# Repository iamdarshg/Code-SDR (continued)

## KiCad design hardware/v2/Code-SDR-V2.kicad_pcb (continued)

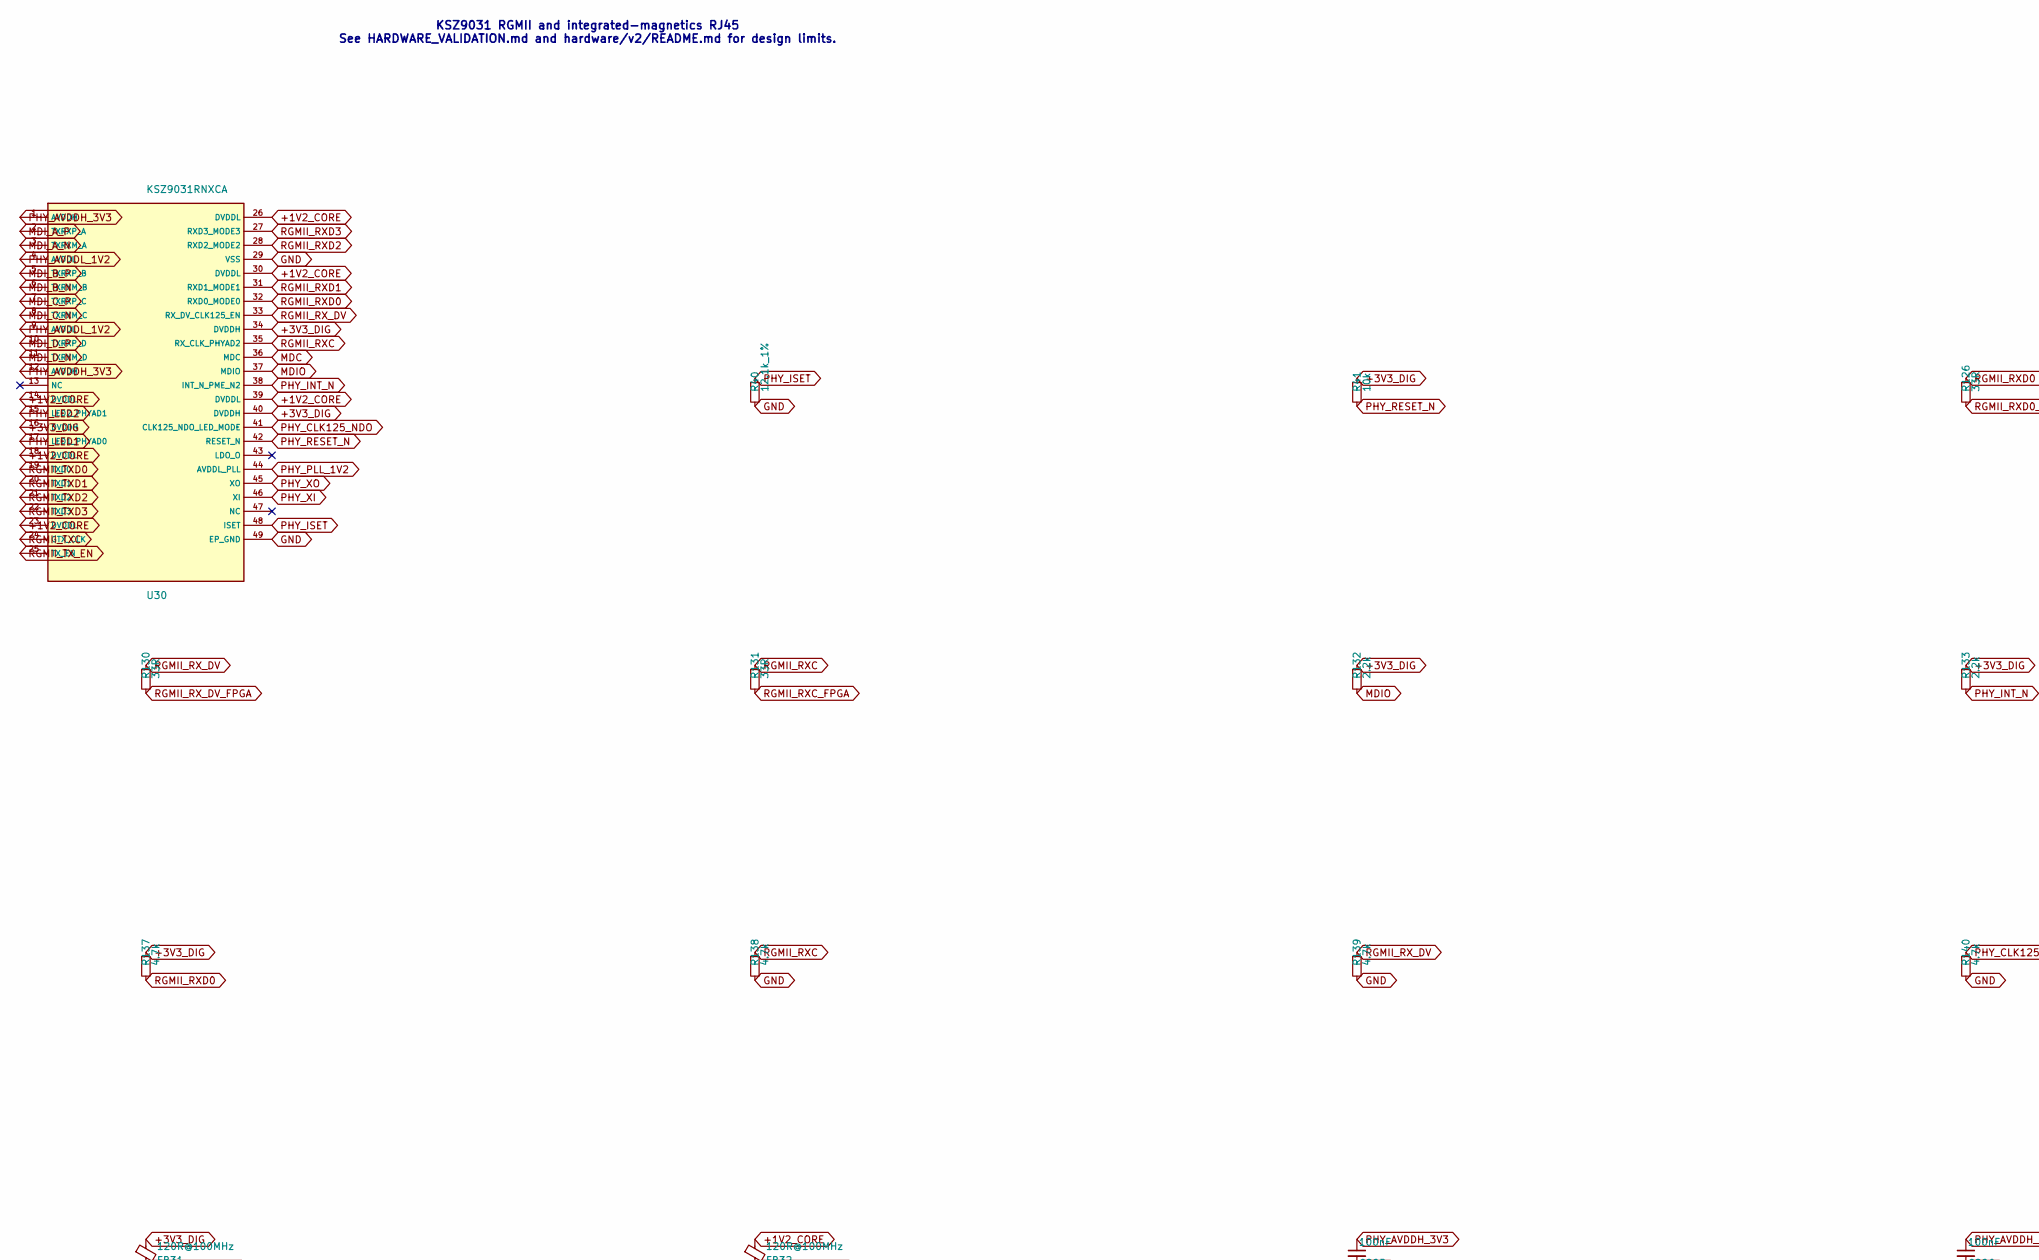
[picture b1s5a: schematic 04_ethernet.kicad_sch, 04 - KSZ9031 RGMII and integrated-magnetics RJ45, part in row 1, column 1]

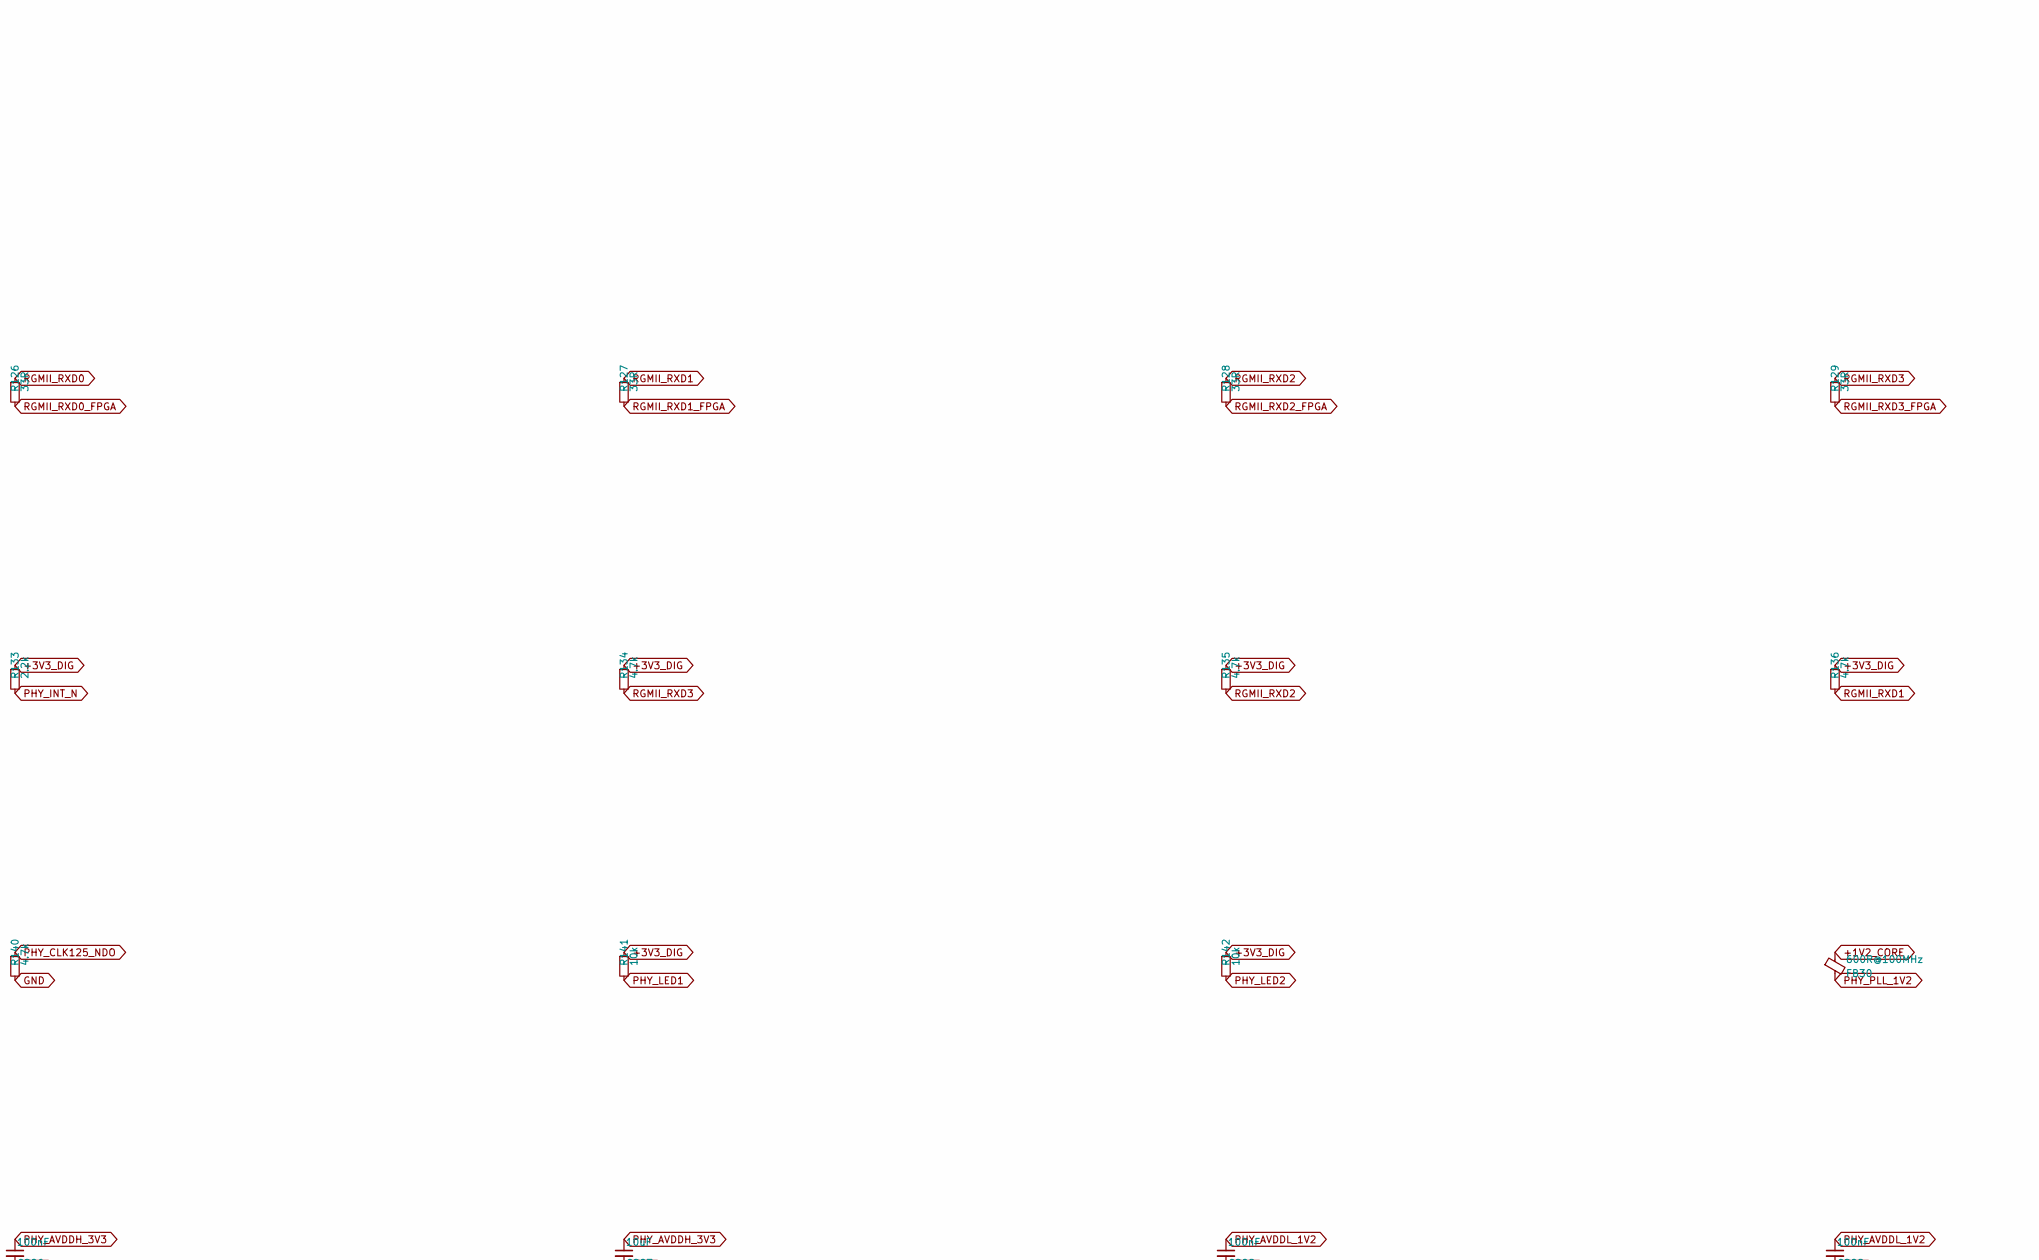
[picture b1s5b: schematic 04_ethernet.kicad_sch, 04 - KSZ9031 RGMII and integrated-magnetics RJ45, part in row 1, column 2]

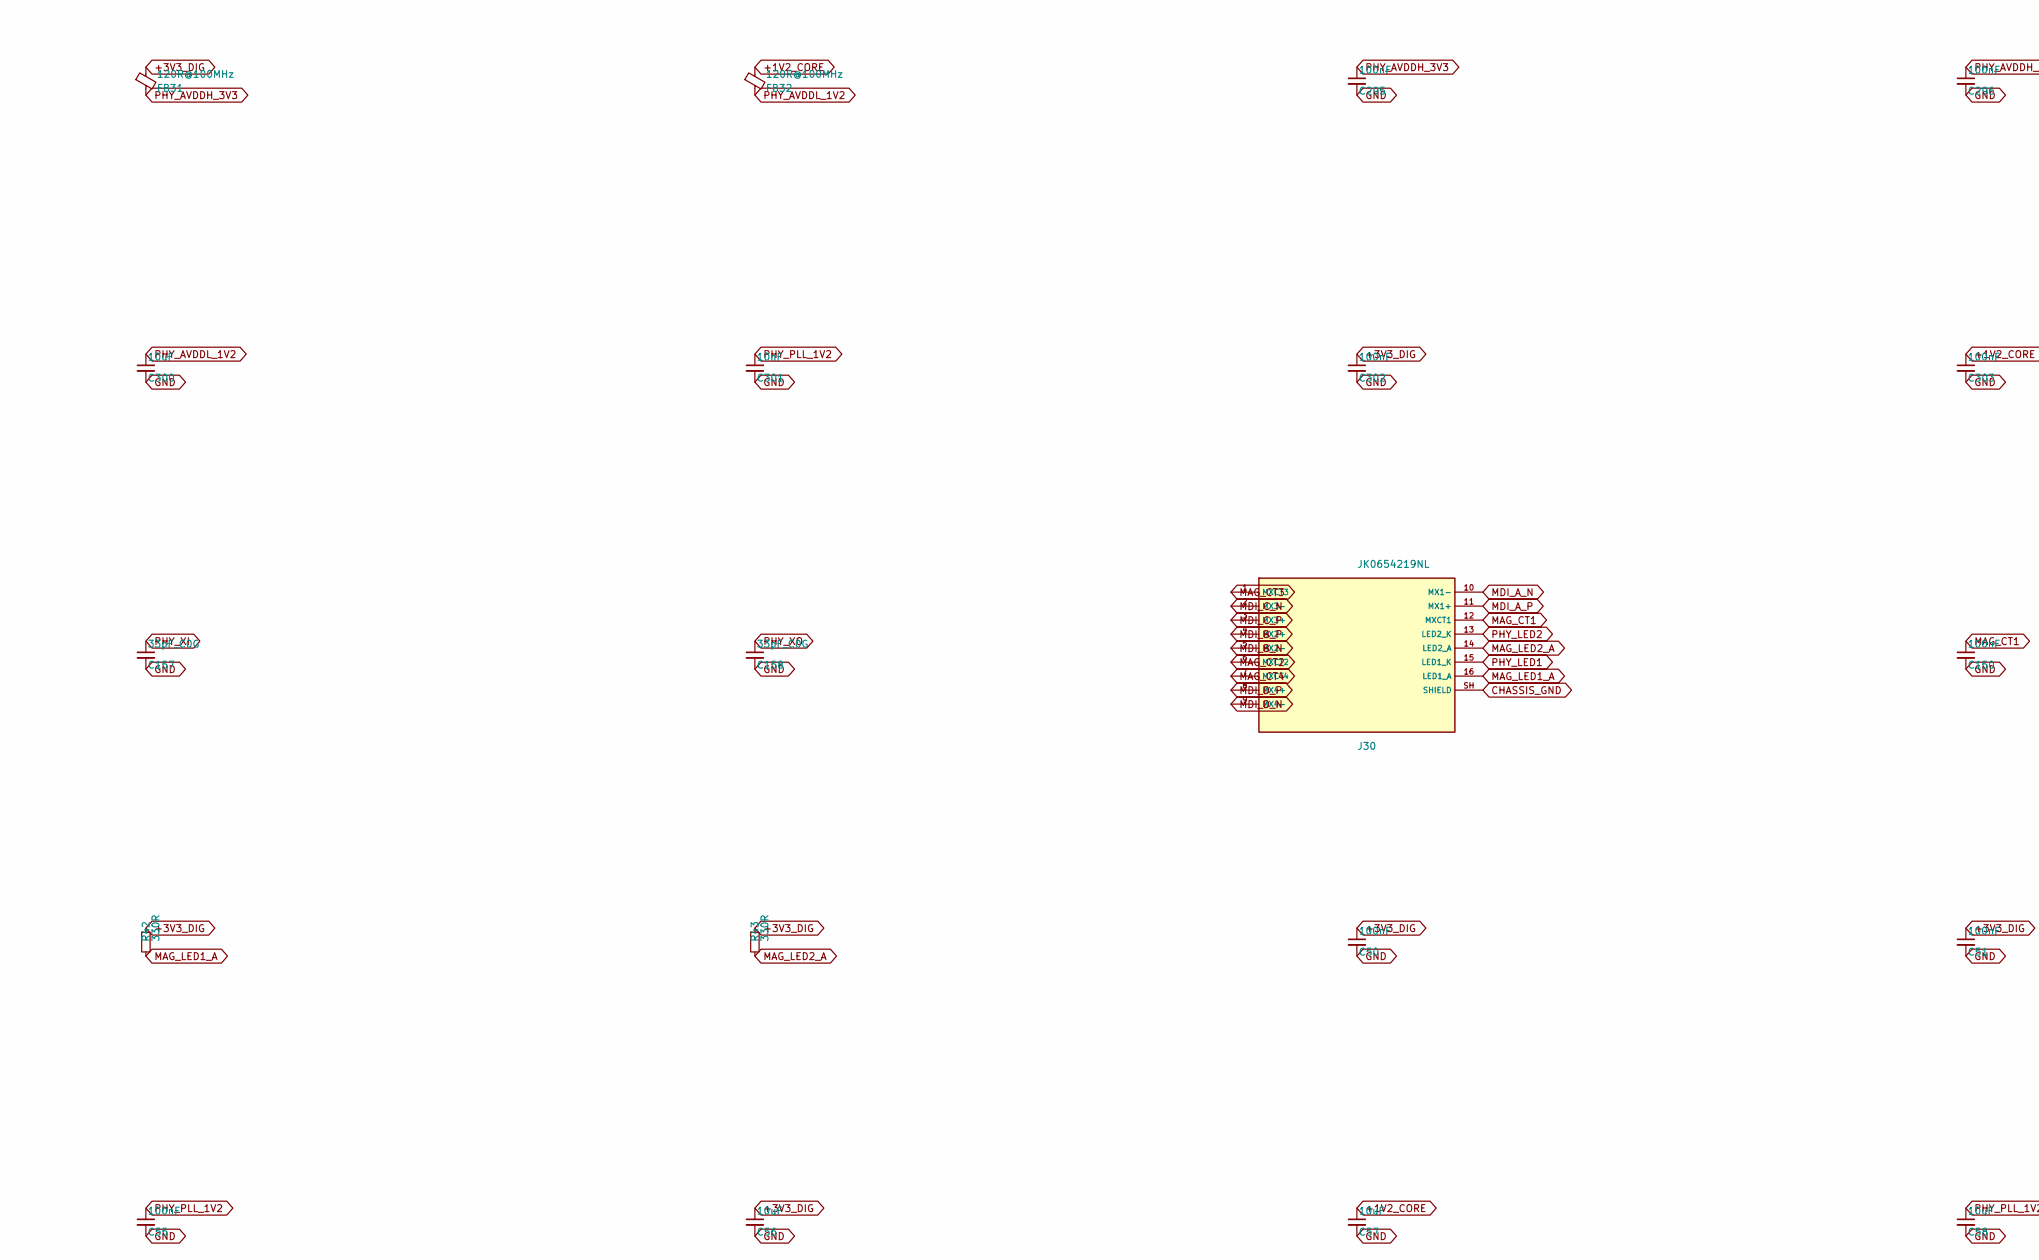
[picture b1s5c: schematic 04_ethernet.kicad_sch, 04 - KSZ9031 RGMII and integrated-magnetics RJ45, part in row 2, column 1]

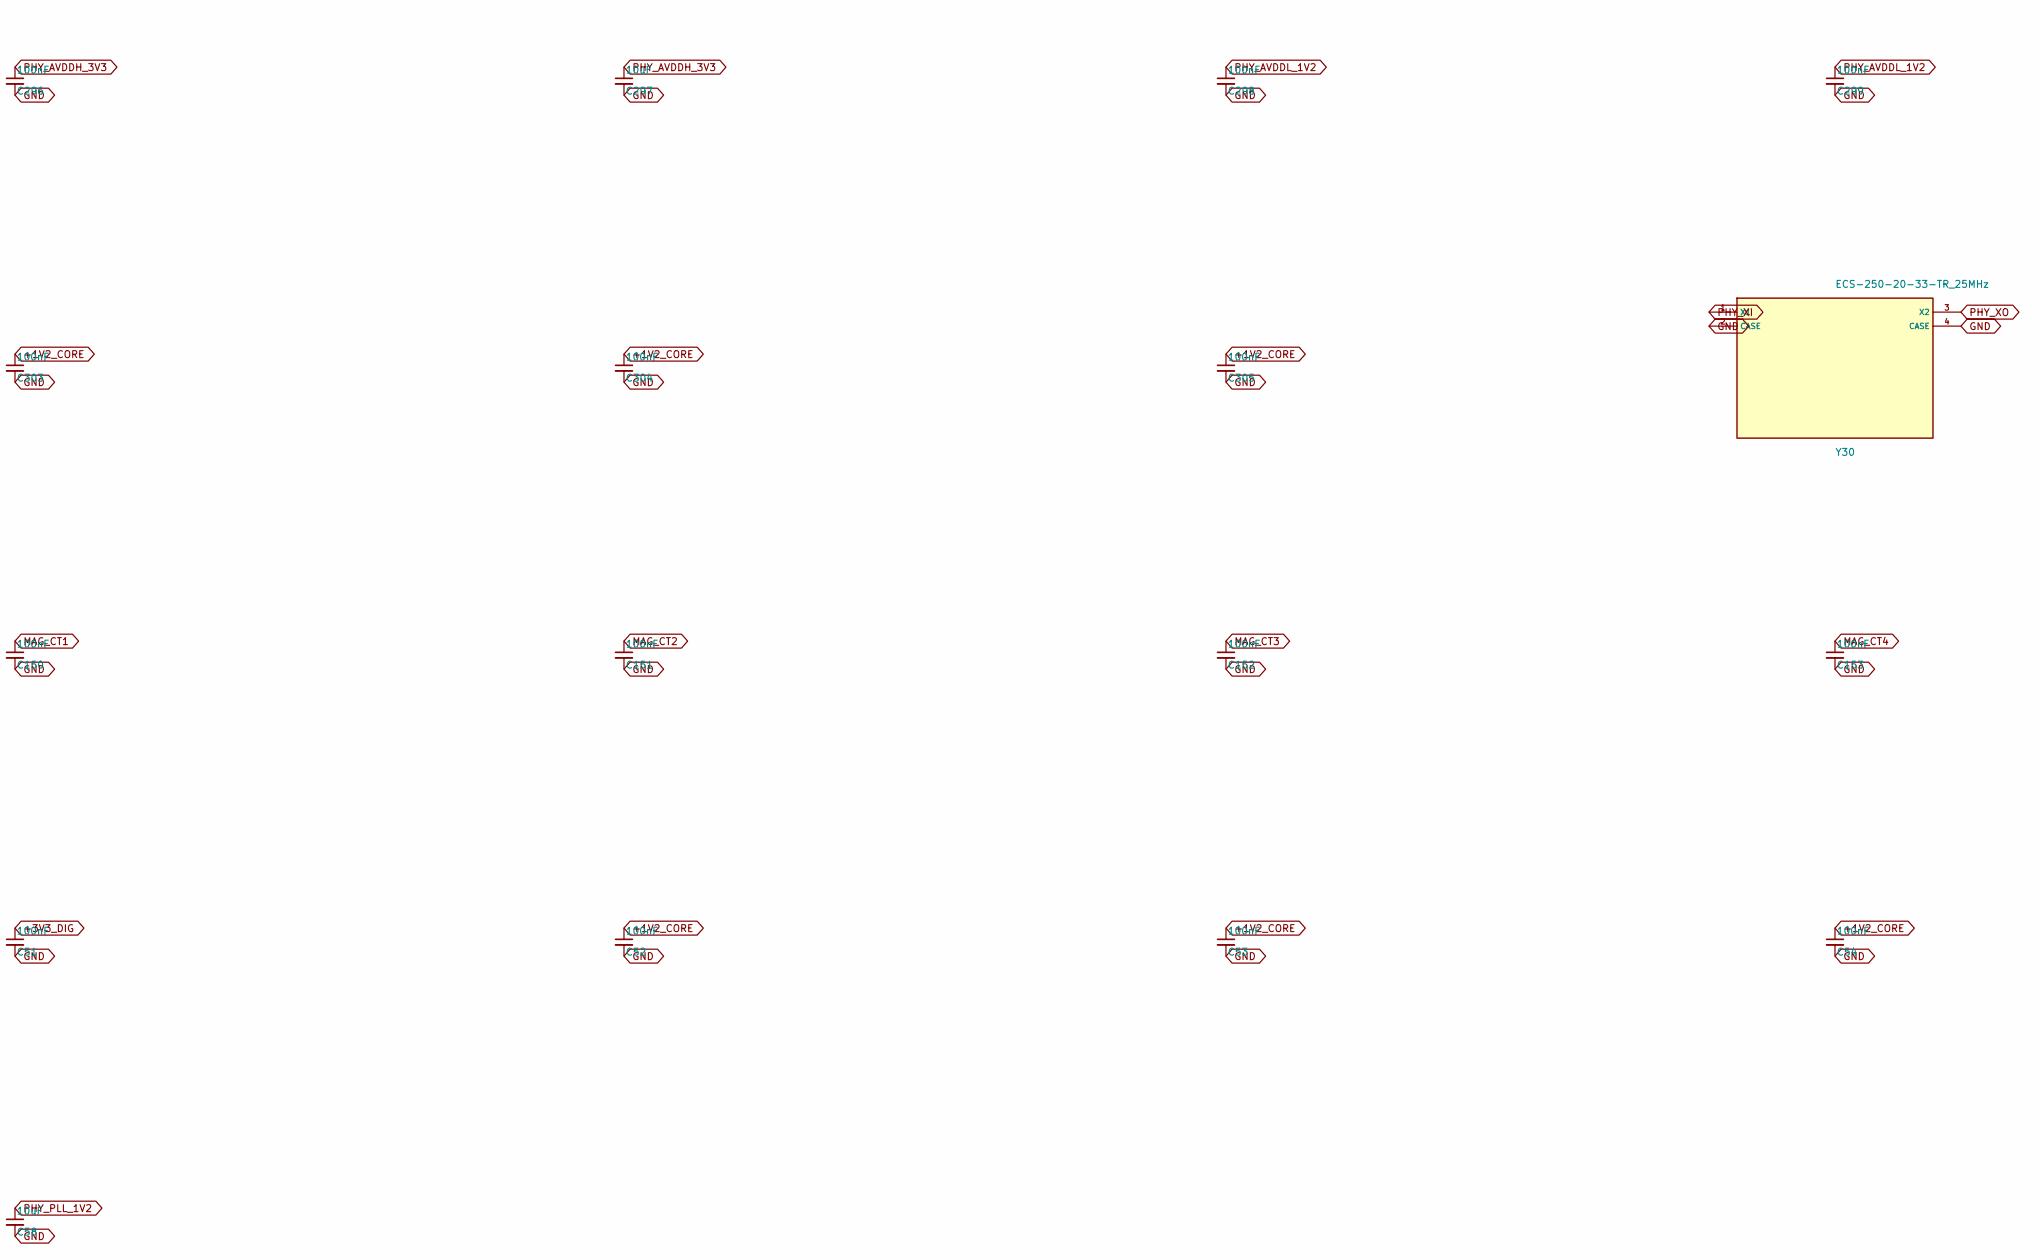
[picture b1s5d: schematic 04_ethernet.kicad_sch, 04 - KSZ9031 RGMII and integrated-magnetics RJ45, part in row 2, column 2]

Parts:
C50, C51, C52, C53, C54, C55, C150, C151, C152, C153, C295, C296, C298, C299, C302, C303, C304, C305: 100nF; C_0402_1005Metric
C56, C57, C58, C297, C300: 10uF; C_0805_2012Metric
C157, C158: 33pF_C0G; C_0402_1005Metric
C301: 10nF; C_0402_1005Metric
FB30: 600R@100MHz; L_0603_1608Metric_Pad1.05x0.95mm_HandSolder
FB31, FB32: 120R@100MHz; L_0603_1608Metric_Pad1.05x0.95mm_HandSolder
J30: JK0654219NL; RJ45_Pulse_JK0654219NL_Horizontal
R40: 12.1k_1%; R_0402_1005Metric
R41, R141, R142: 10k; R_0402_1005Metric
R42, R43: 330R; R_0402_1005Metric
R126, R127, R128, R129, R130, R131: 33R; R_0402_1005Metric
R132, R133: 2.2k; R_0402_1005Metric
R134, R135, R136, R137, R138, R139, R140: 4.7k; R_0402_1005Metric
U30: KSZ9031RNXCA; QFN-48-1EP_7x7mm_P0.5mm_EP3.5x3.5mm_ThermalVias
Y30: ECS-250-20-33-TR_25MHz; Crystal_SMD_3225-4Pin_3.2x2.5mm

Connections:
+1V2_CORE: C52.1, C53.1, C54.1, C57.1, C303.1, C304.1, C305.1, FB30.1, FB32.1, U30.14 (DVDDL), U30.18 (DVDDL), U30.23 (DVDDL), U30.26 (DVDDL), U30.30 (DVDDL), U30.39 (DVDDL); also elsewhere on the board
CHASSIS_GND: J30.SH (SHIELD); also elsewhere on the board
MAG_CT1: C150.1, J30.12 (MXCT1)
MAG_CT2: C151.1, J30.6 (MXCT2)
MAG_CT3: C152.1, J30.1 (MXCT3)
MAG_CT4: C153.1, J30.7 (MXCT4)
MAG_LED1_A: J30.16 (LED1_A), R42.2
MAG_LED2_A: J30.14 (LED2_A), R43.2
MDC: U30.36 (MDC); also elsewhere on the board
MDIO: R132.2, U30.37 (MDIO); also elsewhere on the board
MDI_A_N: J30.10 (MX1-), U30.3 (TXRXM_A)
MDI_A_P: J30.11 (MX1+), U30.2 (TXRXP_A)
MDI_B_N: J30.5 (MX2-), U30.6 (TXRXM_B)
MDI_B_P: J30.4 (MX2+), U30.5 (TXRXP_B)
MDI_C_N: J30.2 (MX3-), U30.8 (TXRXM_C)
MDI_C_P: J30.3 (MX3+), U30.7 (TXRXP_C)
MDI_D_N: J30.9 (MX4-), U30.11 (TXRXM_D)
MDI_D_P: J30.8 (MX4+), U30.10 (TXRXP_D)
PHY_AVDDH_3V3: C295.1, C296.1, C297.1, FB31.2, U30.1 (AVDDH), U30.12 (AVDDH)
PHY_AVDDL_1V2: C298.1, C299.1, C300.1, FB32.2, U30.4 (AVDDL), U30.9 (AVDDL); also elsewhere on the board
PHY_CLK125_NDO: R140.1, U30.41 (CLK125_NDO_LED_MODE)
PHY_INT_N: R133.2, U30.38 (INT_N_PME_N2); also elsewhere on the board
PHY_ISET: R40.1, U30.48 (ISET)
PHY_LED1: J30.15 (LED1_K), R141.2, U30.17 (LED1_PHYAD0)
PHY_LED2: J30.13 (LED2_K), R142.2, U30.15 (LED2_PHYAD1)
PHY_PLL_1V2: C55.1, C58.1, C301.1, FB30.2, U30.44 (AVDDL_PLL)
PHY_RESET_N: R41.2, U30.42 (RESET_N); also elsewhere on the board
PHY_XI: C157.1, U30.46 (XI), Y30.1 (X1)
PHY_XO: C158.1, U30.45 (XO), Y30.3 (X2)
RGMII_RXC: R131.1, R138.1, U30.35 (RX_CLK_PHYAD2)
RGMII_RXC_FPGA: R131.2; also elsewhere on the board
RGMII_RXD0: R126.1, R137.2, U30.32 (RXD0_MODE0)
RGMII_RXD0_FPGA: R126.2; also elsewhere on the board
RGMII_RXD1: R127.1, R136.2, U30.31 (RXD1_MODE1)
RGMII_RXD1_FPGA: R127.2; also elsewhere on the board
RGMII_RXD2: R128.1, R135.2, U30.28 (RXD2_MODE2)
RGMII_RXD2_FPGA: R128.2; also elsewhere on the board
RGMII_RXD3: R129.1, R134.2, U30.27 (RXD3_MODE3)
RGMII_RXD3_FPGA: R129.2; also elsewhere on the board
RGMII_RX_DV: R130.1, R139.1, U30.33 (RX_DV_CLK125_EN)
RGMII_RX_DV_FPGA: R130.2; also elsewhere on the board
RGMII_TXC: U30.24 (GTX_CLK); also elsewhere on the board
RGMII_TXD0: U30.19 (TXD0); also elsewhere on the board
RGMII_TXD1: U30.20 (TXD1); also elsewhere on the board
RGMII_TXD2: U30.21 (TXD2); also elsewhere on the board
RGMII_TXD3: U30.22 (TXD3); also elsewhere on the board
RGMII_TX_EN: U30.25 (TX_EN); also elsewhere on the board

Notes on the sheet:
KSZ9031 RGMII and integrated-magnetics RJ45 See HARDWARE_VALIDATION.md and hardware/v2/README.md for design limits.
